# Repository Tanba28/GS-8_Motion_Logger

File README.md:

# GS-8_Motion_Logger
GS-8 Motion Logger. 6 Axis Logger.

Master project -> [project-arrows/GS-8](https://github.com/project-arrows/GS-8)

## Overview
 * GS-8 6軸ロガー

## Role
 * 加速度をロギングする。
 * 角速度をロギングする。

## Link
 * [Tanba28/GS-8_PM_Board](https://github.com/Tanba28/GS-8_PM_Board)
 * [Tanba28/GS-8_PD_Board](https://github.com/Tanba28/GS-8_PD_Board)
 * [Tanba28/GS-8_Barometer](https://github.com/Tanba28/GS-8_Barometer)
 * [Tanba28/GS-8_Relay_Board](https://github.com/Tanba28/GS-8_Relay_Board)
 * [ringo156/GS-8_ACCLRM_Board](https://github.com/ringo156/GS-8_ACCLRM_Board)
 * [takamasavvv/RCT-X_Logger](https://github.com/takamasavvv/RCT-X-Logger)
 * [takamasavvv/RCT-X-Telemetry](https://github.com/takamasavvv/RCT-X-Telemetry)
 
## LICENSE
MIT License

Copyright (c) 2019 Tanba28

Permission is hereby granted, free of charge, to any person obtaining a copy
of this software and associated documentation files (the "Software"), to deal
in the Software without restriction, including without limitation the rights
to use, copy, modify, merge, publish, distribute, sublicense, and/or sell
copies of the Software, and to permit persons to whom the Software is
furnished to do so, subject to the following conditions:

The above copyright notice and this permission notice shall be included in all
copies or substantial portions of the Software.

THE SOFTWARE IS PROVIDED "AS IS", WITHOUT WARRANTY OF ANY KIND, EXPRESS OR
IMPLIED, INCLUDING BUT NOT LIMITED TO THE WARRANTIES OF MERCHANTABILITY,
FITNESS FOR A PARTICULAR PURPOSE AND NONINFRINGEMENT. IN NO EVENT SHALL THE
AUTHORS OR COPYRIGHT HOLDERS BE LIABLE FOR ANY CLAIM, DAMAGES OR OTHER
LIABILITY, WHETHER IN AN ACTION OF CONTRACT, TORT OR OTHERWISE, ARISING FROM,
OUT OF OR IN CONNECTION WITH THE SOFTWARE OR THE USE OR OTHER DEALINGS IN THE
SOFTWARE.

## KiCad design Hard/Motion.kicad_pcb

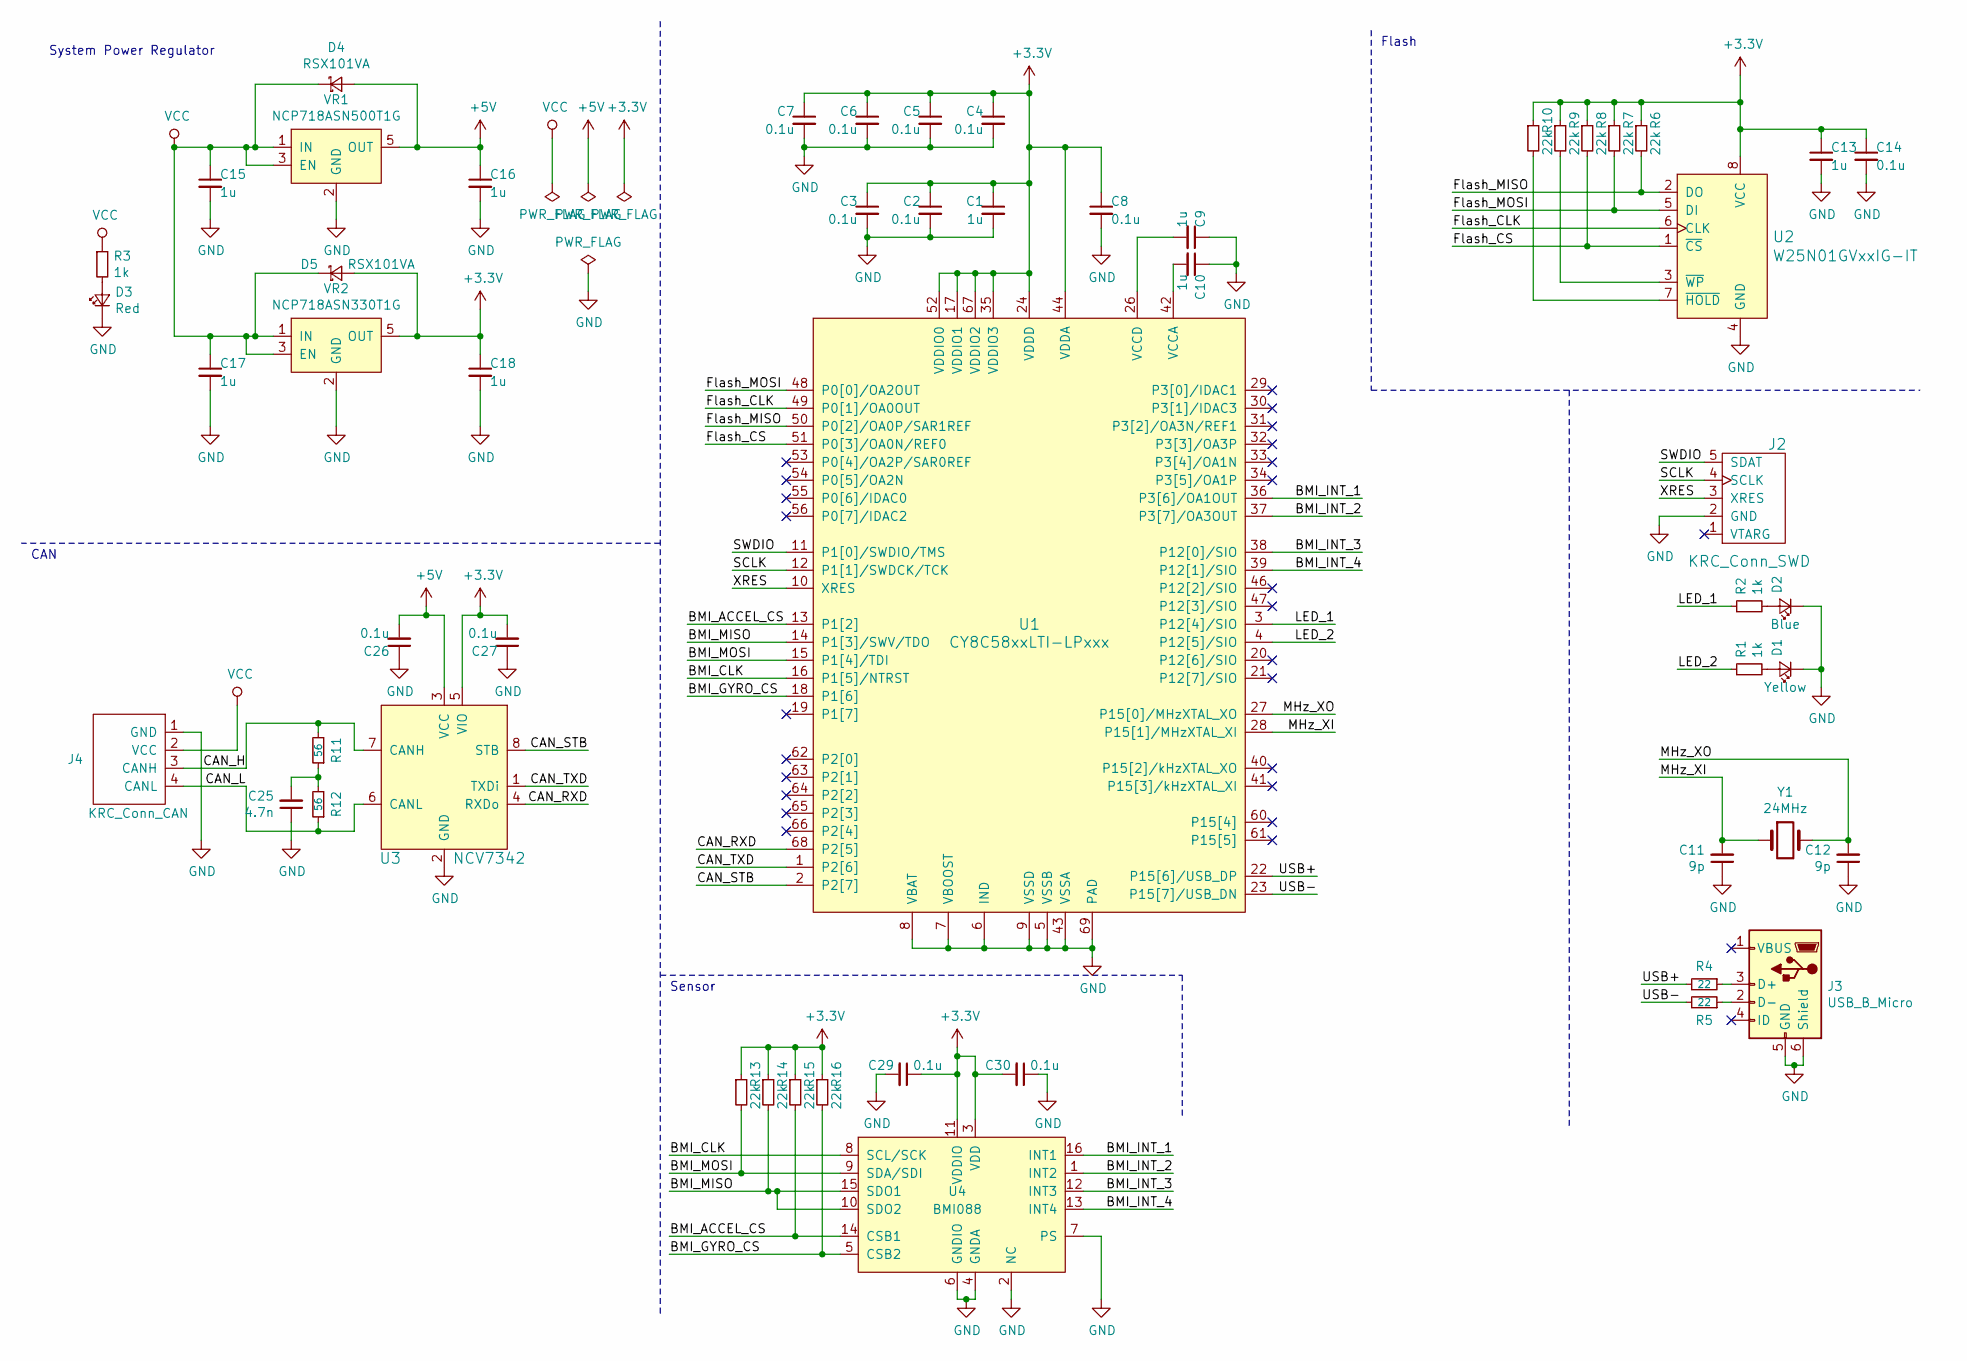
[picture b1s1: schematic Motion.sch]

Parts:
C1, C9, C10, C13, C15, C16, C17, C18: 1u; C_0402_1005Metric; MPN GRM155R61E105KA12D
C2, C3, C4, C5, C6, C7, C8, C14, C26, C27, C29, C30: 0.1u; C_0402_1005Metric; MPN GRM155R62A104KE14D
C11, C12: 9p; C_0402_1005Metric; MPN GRM1555C1H9R0DA01D
C25: 4.7n; C_0402_1005Metric; MPN GRM155R71H472KA01D
D1: Yellow; LED_0603_1608Metric
D2: Blue; LED_0603_1608Metric
D3: Red; LED_0603_1608Metric
D4, D5: RSX101VA; D_TUMD2; MPN RSX101VAM-30TR
J2: KRC_Conn_SWD; JST_JQ_05JQ-BT_1x05_P2.5mm_Vertical; MPN 05JQ-BT
J3: USB_B_Micro; Hirose_ZX_ZX62D-B-5P8; MPN ZX62D-B-5P8(30)
J4: KRC_Conn_CAN; JST_XH_S4B-XH-A_1x04_P2.50mm_Horizontal; MPN S4B-XH-A
R1, R2, R3: 1k; R_0402_1005Metric; MPN ERJ-2GEJ102X
R4, R5: 22; R_0402_1005Metric; MPN ERJ-2GEJ220X
R6, R7, R8, R9, R10, R13, R14, R15, R16: 22k; R_0402_1005Metric; MPN ERJ-2RKF2202X
R11, R12: 56; R_0402_1005Metric; MPN ERJ-2GEJ560X
U1: CY8C58xxLTI-LPxxx; Cypress_QFN-68_EP_8x8_Pitch0.4mm; MPN CY8C5868LTI-LP039
U2: W25N01GVxxIG-IT; WSON-8_8x6mm_P1.27mm; MPN W25N01GVZEIG TR
U3: NCV7342; DFN-8-1EP_3x3mm_P0.65mm_EP1.55x2.4mm; MPN NCV7342MW3R2G
U4: BMI088; Bosch_QFN-16_4.5x3.0mm_P0.5mm_Handsoldering
VR1: NCP718ASN500T1G; TSOT-23-5; MPN NCP718ASN500T1G
VR2: NCP718ASN330T1G; TSOT-23-5; MPN NCP718ASN330T1G
Y1: 24MHz; Crystal_Murata_XRCHA; MPN XRCHA24M000F0A01R0

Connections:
+3V3: C1.1, C2.1, C3.1, C4.1, C5.1, C6.1, C7.1, C8.1, C13.1, C14.1, C18.1, C27.2, C29.1, C30.2, D5.2 (A), R6.1, R7.1, R8.1, R9.1, R10.1, R13.1, R14.1, R15.1, R16.1, U1.17 (VDDIO1), U1.24 (VDDD), U1.35 (VDDIO3), U1.44 (VDDA), U1.52 (VDDIO0), U1.59 (VDDD), U1.67 (VDDIO2), U2.8 (VCC), U3.5 (VIO), U4.3 (VDD), U4.11 (VDDIO), VR2.5 (OUT)
+5V: C16.1, C26.2, D4.2 (A), U3.3 (VCC), VR1.5 (OUT)
/BMI_ACCEL_CS: R15.2, U1.13 (P1[2]), U4.14 (CSB1)
/BMI_CLK: U1.16 (P1[5]/NTRST), U4.8 (SCL/SCK)
/BMI_GYRO_CS: R16.2, U1.18 (P1[6]), U4.5 (CSB2)
/BMI_INT_1: U1.36 (P3[6]/OA1OUT), U4.16 (INT1)
/BMI_INT_2: U1.37 (P3[7]/OA3OUT), U4.1 (INT2)
/BMI_INT_3: U1.38 (P12[0]/SIO), U4.12 (INT3)
/BMI_INT_4: U1.39 (P12[1]/SIO), U4.13 (INT4)
/BMI_MISO: R14.2, U1.14 (P1[3]/SWV/TDO), U4.10 (SDO2), U4.15 (SDO1)
/BMI_MOSI: R13.2, U1.15 (P1[4]/TDI), U4.9 (SDA/SDI)
/CAN_H: J4.3 (CANH), R11.2, U3.7 (CANH)
/CAN_L: J4.4 (CANL), R12.1, U3.6 (CANL)
/CAN_RXD: U1.68 (P2[5]), U3.4 (RXDo)
/CAN_STB: U1.2 (P2[7]), U3.8 (STB)
/CAN_TXD: U1.1 (P2[6]), U3.1 (TXDi)
/Flash_CLK: U1.49 (P0[1]/OA0OUT), U2.6 (CLK)
/Flash_CS: R8.2, U1.51 (P0[3]/OA0N/REF0), U2.1 (~CS)
/Flash_MISO: R6.2, U1.50 (P0[2]/OA0P/SAR1REF), U2.2 (DO)
/Flash_MOSI: R7.2, U1.48 (P0[0]/OA2OUT), U2.5 (DI)
/LED_1: R2.1, U1.3 (P12[4]/SIO)
/LED_2: R1.1, U1.4 (P12[5]/SIO)
/MHz_XI: C11.2, U1.28 (P15[1]/MHzXTAL_XI), Y1.1
/MHz_XO: C12.2, U1.27 (P15[0]/MHzXTAL_XO), Y1.2
/SCLK: J2.4 (SCLK), U1.12 (P1[1]/SWDCK/TCK)
/SWDIO: J2.5 (SDAT), U1.11 (P1[0]/SWDIO/TMS)
/USB+: R4.2, U1.22 (P15[6]/USB_DP)
/USB-: R5.2, U1.23 (P15[7]/USB_DN)
/XRES: J2.3 (XRES), U1.10 (XRES)
GND: C1.2, C2.2, C3.2, C4.2, C5.2, C6.2, C7.2, C8.2, C9.1, C10.1, C11.1, C12.1, C13.2, C14.2, C15.2, C16.2, C17.2, C18.2, C25.1, C26.1, C27.1, C29.2, C30.1, D1.1 (K), D2.1 (K), D3.1 (K), J2.2 (GND), J3.5 (GND), J3.6 (Shield), J4.1 (GND), U1.5 (VSSB), U1.6 (IND), U1.7 (VBOOST), U1.8 (VBAT), U1.9 (VSSD), U1.25 (VSSD), U1.43 (VSSA), U1.45 (VSSD), U1.58 (VSSD), U1.69 (PAD), U2.4 (GND), U2.9, U3.2 (GND), U3.9, U4.2 (NC), U4.4 (GNDA), U4.6 (GNDIO), U4.7 (PS), VR1.2 (GND), VR2.2 (GND)
unnamed: C9.2, U1.26 (VCCD), U1.57 (VCCD)
unnamed: C10.2, U1.42 (VCCA)
unnamed: C25.2, R11.1, R12.2
unnamed: D1.2 (A), R1.2
unnamed: D2.2 (A), R2.2
unnamed: D3.2 (A), R3.2
unnamed: J3.2 (D-), R5.1
unnamed: J3.3 (D+), R4.1
unnamed: R9.2, U2.3 (~WP)
unnamed: R10.2, U2.7 (~HOLD)
VCC: C15.1, C17.1, D4.1 (K), D5.1 (K), J4.2 (VCC), R3.1, VR1.1 (IN), VR1.3 (EN), VR2.1 (IN), VR2.3 (EN)

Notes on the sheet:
System Power Regulator
Flash
Sensor
CAN

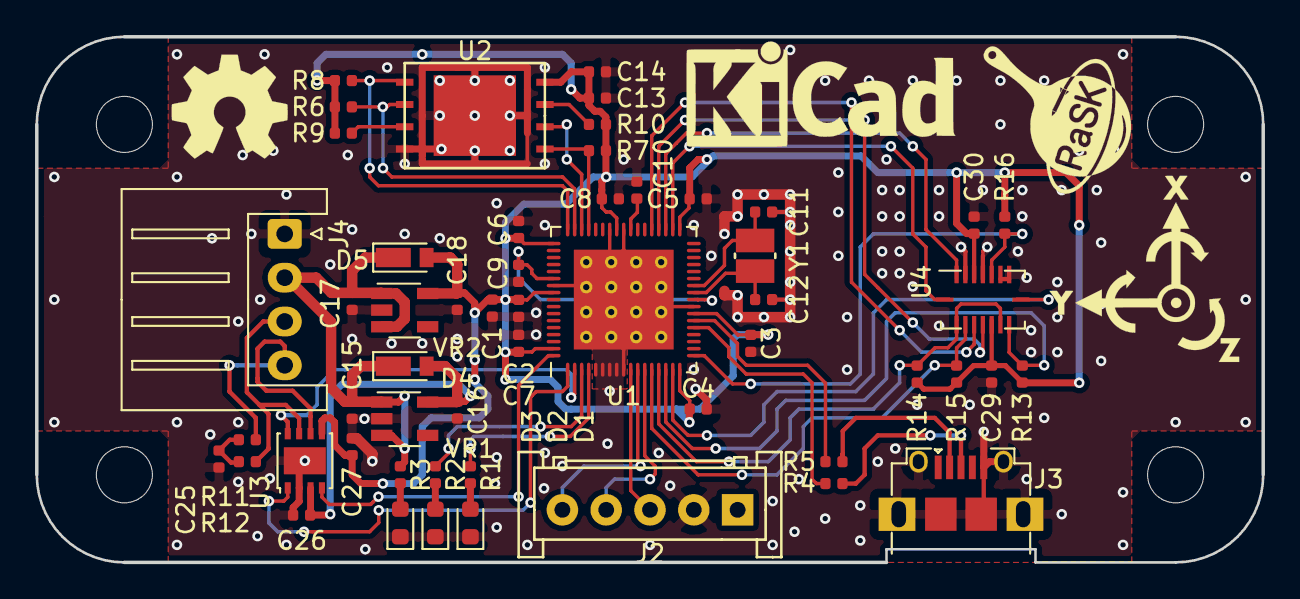
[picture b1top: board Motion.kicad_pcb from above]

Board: 2 copper layers, 70.0 x 30.0 mm, 54 parts (0 on the bottom side), 41 nets.

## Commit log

2019-10-12 [add] ハード完成. ガーバー出力
2019-10-12 [update] READMEを整備
